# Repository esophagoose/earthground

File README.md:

# earthground: A Python Library for Creating Software-Defined Electrical Designs

## Overview
Earthground encompasses a comprehensive suite of tools and libraries aimed at facilitating software-defined electronic schematics.

[Documentation](https://earthground.readthedocs.io/en/latest/)

## Getting Started
### Setup
```
pip install earthground
```

### Simple Example - Resistor Divider

```
import earthground.exporters.kicad
import earthground.components as cmp
import earthground.library.headers.connectors as conn_lib
import earthground.schematic as sch_lib
import earthground.standard_values as sv

# Setup the schematic page
schematic = sch_lib.Design("Resistor Divider Example")
schematic.default_passive_size = "0603"

# Create the components
r1, r2 = sv.find_closest_ratio(5 / 3.3)  # finds closest values in E24
r_top = schematic.add_component(cmp.Resistor(f"{r1}k"))
r_bottom = schematic.add_component(cmp.Resistor(f"{r2}k"))
input_connector = schematic.add_component(conn_lib.standard_0_1_inch_header(pin_count=2))
output_connector = schematic.add_component(conn_lib.standard_0_1_inch_header(pin_count=2))

# Connect them and print schematic to console
schematic.connect([r_top.pins[1], input_connector.pins[1]], "SIG_5V0")
schematic.connect([r_top.pins[2], r_bottom.pins[1], output_connector.pins[1]], "SIG_3V3")
schematic.connect([input_connector.pins[2], r_bottom.pins[2], output_connector.pins[2]], "GND")
schematic.print()

# Export the layout to KiCad
earthground.exporters.kicad.KicadExporter(schematic).save()
```

## Export Pipeline
This is the minimal flow from schematic to KiCad layout.
- Build a `sch_lib.Design` and add components.
- Create a `KicadExporter` from `earthground/exporters/kicad.py`.
- Optionally pass `positions` to override footprint placement and reference text.
- Call `.save()` to emit the `.kicad_pcb`.

The `positions` override format is a dict keyed by refdes. Each value can be a `base.Position` or a concise dict.
- `{"at": (x, y, rot)}` moves the footprint.
- `{"ref_at": (x, y, rot)}` moves the reference text.

Example:
```
positions = {
    "R1": {"at": (10.0, 5.0, 90.0), "ref_at": (8.0, 5.0, 90.0)},
}
earthground.exporters.kicad.KicadExporter(schematic, positions=positions).save()
```

### Project Walkthrough - 32 Port I/O Expander

[Read the example](https://github.com/esophagoose/earthground/tree/main/examples)
- Located in ``examples/io_expander_example.py``
- Run using: ``uv run -m examples.io_expander_example``

## Advantages of Software-Defined Circuits
### Extensive Tooling
Text-based schematics means engineers can leverage existing software engineering tooling to create error-free designs faster
- Use version control software to save progress, create easy-to-read diffs between versions, and do design review
- Use dev tooling like CI/CD tools to automatically run design rule checkers and application-specific validators to ensure a correct design
- One-click releases - Automatically generate Gerbers, pick-n-place files, cost rollups, power budgets, bringup test plans
### Modular
Finally have stable and correct part libraries and circuits that you can quickly piece together to create complex projects quickly
### Extendable
Earthground can be extended to many purposes because it's written in Python
- If your PCB being connecting to another PCB via harness, you could write an exporter so your favorite harness program always has the latest design
- If there's a microcontroller in your design, you could add an exporter to generate a BSP package or Micropython definition from the schematic that will automatically create a new file on every revision
- If you are concerned about supply chain and components going out-of-stock, you could have your schematic track which components are in stock and define part variations
### Powerful
With a Python backend, it's simple to create powerful component libraries that allow you to create complex designs quickly. Just read the datasheet once and you are good to go
- Abstract complex hardware configuration pins to the component library so your schematics are highly readable (and therefore easily reviewable)
- Rather than noting the position of every configuration on a microcontroller and matching it to the datasheet for every design review you do. You could review your component definition once then in every design do readable things like `mcu.set_boot_location(mcu.EXTERNAL_FLASH)` to easily catch issues
- Quickly set addresses are know they are right:
    ```
    for i, device in enumerate(i2c_devices):
        device.set_i2c_address(i)
    ```
- Add validators for datasheet errata and buried issues so if anyone uses a component in a nonrecommended way on the current design or any future design, Earthground will flag it.
- Parameterize passive component selection for ICs
- For buck converters, Earthground can automatically size inductors based on datasheet parameters
- For LDOs, given an output voltage, Earthground will select the feedback resistors, round them to E24 values, and warn you if the result output voltage is beyond a specified percentage

## Workflows
 - Work on small subcircuits in a design
 - Export to KiCad and make a standardized layout
 - Use `uv run -m earthground.tools.get_kicad_layout` to generate a structured layout
 - Add that to the design
 - Add those building blocks to the full design

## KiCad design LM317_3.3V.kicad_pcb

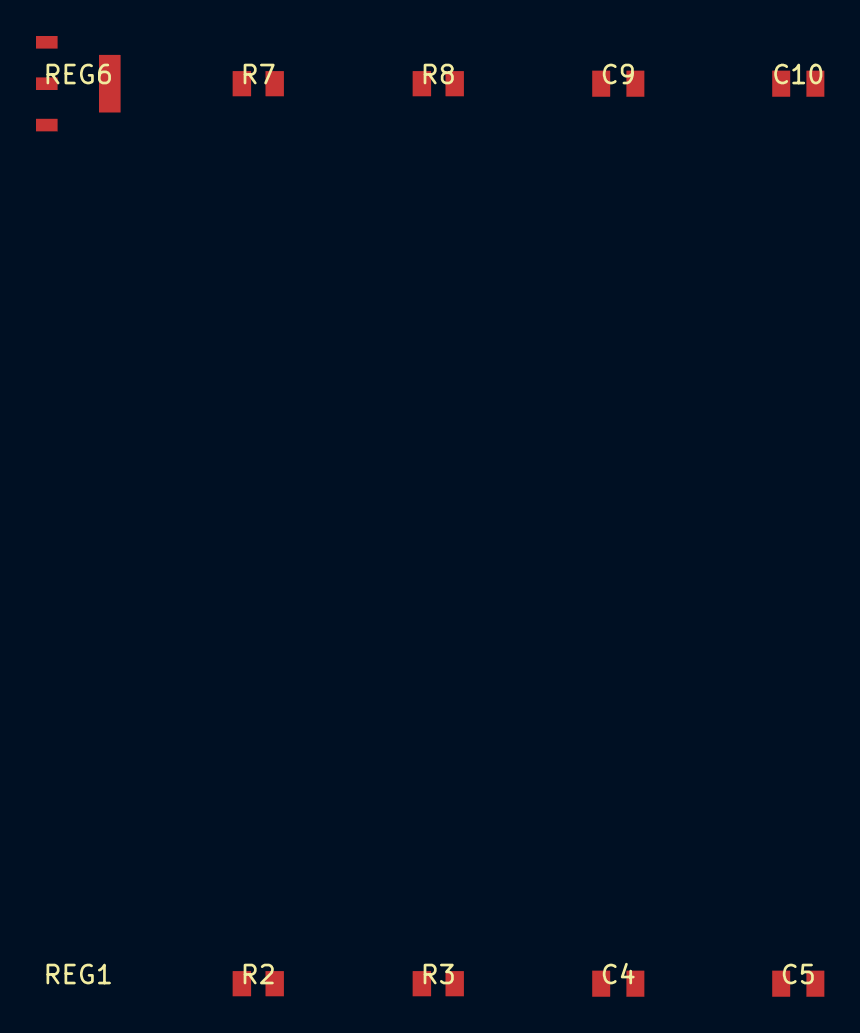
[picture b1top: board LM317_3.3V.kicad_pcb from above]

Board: 2 copper layers, 10 parts (1 on the bottom side), 8 nets, no tracks yet.

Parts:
C4, C9: C0805; CAP_100.0nF_50.0V
C5, C10: C0805; CAP_1.0uF_10.0V
R2, R7: R0805; RES_240.0Ω
R3, R8: R0805; RES_394.0Ω
REG1, REG6: SOT-223; LM317AMDTX

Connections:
ADJ_FB: R2.2, R3.1, REG1.1
GND: C4.2, C5.2, R3.2
LM3170_ADJ_FB: R7.2, R8.1, REG6.1
LM3170_GND: C9.2, C10.2, R8.2
LM3170_VIN: C9.1, REG6.3
LM3170_VOUT: C10.1, R7.1, REG6.2, REG6.4
VIN: C4.1, REG1.3
VOUT: C5.1, R2.1, REG1.2, REG1.4

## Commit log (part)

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2024-02-08 Updated README to explain the project
2024-02-08 Initial commit of files
2024-02-09 Refactored pygerber and example code is working
2024-02-11 Updated README to no longer have pygerber as a submodule
2024-02-11 Added utilities file
2024-02-11 first pass of UI done
2024-02-24 Many backend changes on how nets and modules are handled. Cleaned up example
2024-02-24 Removed WIP layout editor
2024-02-26 Added TMC2100 motor driver
2024-02-28 Bug fixes
2024-02-28 Refactored nets to be only in designs
2024-02-28 Added unit tests
2024-02-28 Fixed bug where connect_bus always assigns a new index
2024-02-29 Squashed some bugs and wrote unit tests for them
2024-02-29 Added readthedocs
2024-02-29 Forgot OS in rtd
2024-03-01 Added more docs and docstrings to schematic.py
2024-03-01 Attempt 1 at fixing imports
2024-03-01 formatting
2024-03-01 fix imports:
2024-03-01 more changes
2024-03-01 More edits
2024-03-02 Added quickstart
2024-03-02 fixed return order on find_closest_ratio
2024-03-02 missing import
2024-03-02 try again
2024-03-02 add parser for Markdown
2024-03-02 Fixed file path
2024-03-02 another try
2024-03-03 finalized first pass of documentation
2024-03-03 Added components
2024-03-03 Ran linter
2024-03-03 Added readthedocs Documentation
    Added readthedocs integration
    Added docs folder
    Wrote docstrings for all schematic.py and components.py
    Gave more examples of using Earthground
    https://earthground.readthedocs.io/en/latest/
2024-03-03 Added more unit tests
2024-03-03 Added auto-generated sphinx docs to gitignore
2024-03-04 Added KiCad PCB layout exporter
2024-03-04 Bug fixes: added names to footprints that are missing them; set passives on modules
2024-03-04 Updated example to include layout
2024-03-04 Added exporters to readthedocs
2024-03-04 Added mock for kicad utilites
2024-03-05 Converting to a package
2024-03-05 Changed import statements
2024-03-05 Split library from core
2024-03-05 moved exporter
2024-03-05 Refactored into folder and updated README
2024-03-05 Removed duplicate sections
2024-03-05 Fixed example header
2024-03-05 Fixed bad sed edit
2024-03-05 Added unit test for footprint types (and caught a bug); removed wip layout
2024-03-05 Added unit tests to footprints
2024-03-07 Improved unit tests
2024-03-07 Added pypi toml
2024-03-08 Bug fixes with mbr3
2024-03-16 Update README.md for pypi package
2024-03-17 Removed libraries from gitignore
2024-03-20 Added component for ports, support multiple bus connections, reverted join_net, bug fixes
2024-03-20 Added automatic component creator tool
2024-03-20 Added automatic component creator tool (#2)
2024-03-21 Bug fixes on component creator, refactored connectors
2024-03-23 Exported first project and fixed several bugs with that process
2024-03-23 Added soldermask open
2024-03-26 Fixed bugs in reference design
2024-03-26 Add parameters to BaseFootprint and made sure it was used everywhere; Added custom silk to KiCad exporter
2024-03-26 Added TI footprint
2025-03-30 pausing point
2025-04-05 Cleaned up and sectioned off code
2025-04-05 Added universal caching
2026-01-16 Added more helper functions and removed PlacedComponent class
2026-01-16 Added support for Kicad footprints
2026-01-16 Added flatten tool to schematics, helper functions, and code cleanup
2026-02-04 Added support for structured layout
2026-02-04 Added better pin name sorting for printed outputs
2026-02-04 Made the bounding box algorithm better
2026-02-04 Lots of code cleanup and migrate to pykicad
2026-02-05 Properly handling modules with managed layout
2026-02-05 Added support for module layout
2026-02-13 Added support for multiple layers, pours, vias, and the Layout class
2026-02-15 Added JLCPCB BOM Exporter
2026-02-15 Bug fixes; fixed refdes always incrementing; add layout module
2026-02-15 Fixed bug in calculating bounding box
2026-02-20 Added more components to the library
2026-02-20 Added / updated generic footprints
2026-02-20 Fixed bug where passive package was always the default
2026-02-20 Layout module now auto-assigns place for floating components
2026-02-20 Rewrote exporter to use layout module:
2026-02-20 Added documentation
2026-02-20 Moved definitions to layout.py
2026-02-20 Updated to new version with dependencies
2026-02-20 Moved footprint folder
2026-03-04 Bug fixes and added inductors as a passive
2026-03-04 Swtich to orientation-based positioning
2026-03-04 Updated from design
2026-03-18 Added kicad footprint support, bug fixes, and more helper functions
2026-03-18 docs: add KiCad schematic export design spec
2026-03-18 docs: specify orthogonal schematic routing
2026-03-18 docs: specify grid-spaced route conflict handling
2026-03-21 Improved JST library
2026-03-27 Added placing bottom layer components and fixed bug where modules with id set will error out
2026-03-29 Cleaned up repo
2026-03-29 Added importer for kicad symbols
2026-03-29 Removed unused docs
2026-03-29 Removed unused test data
2026-03-29 Removed extraneous text
2026-03-29 Removed unused examples
2026-03-29 Linted
2026-03-29 Earthground v0.2 (#3)
2026-03-29 Removed example files
2026-03-30 IPC implementation
2026-03-30 IPC implementation (#5)
2026-03-30 Added example
2026-03-30 Fixed bug in starting IPC
2026-03-30 Implemented yaml import and made place_with_kicad a script
2026-03-31 Implemented yaml import and made place_with_kicad a script (#6)
2026-03-31 Added PWM to MCU base
2026-04-02 Added rigid module support
2026-04-02 Added fab layer lines and text
2026-04-02 Bug fixes: IPC would record the positions on unchanged files and Zones working in Kicad
2026-04-02 Bug fix: PWM was mis-prioritized
2026-04-02 Correct refdes placement bug
2026-04-03 Bug fix: preseve custom packages on passives
2026-04-06 Refactored place with kicad to better support modules
2026-04-12 Clearer errors on invalid type in connections
2026-04-12 Switched SiNumber to Decimel instead of float to prevent string conversion bugs
2026-04-12 Improved logging
2026-04-30 Patched bug where non-int indicies were masked
2026-05-02 Added support for Assemblies and Connector Interfaces
2026-05-02 Fixed orphan net bug where multiple connections to design ports doesn't connect them properly
2026-05-02 Exports manufacturer name into the kicad layout
2026-05-04 Fixed place with Kicad rotation bug
2026-05-04 Fixed net propogation bug
2026-05-11 Minor bug fixes
2026-05-13 Added board-to-board connector interface
2026-05-16 Made B2B Interfaces generate a design
2026-05-16 Makes silkscreen optional
2026-05-17 Fixed bug where not all nets were renamed when added as a module
2026-05-17 Fixed bug where no silk doesn't register ref id on footprint
